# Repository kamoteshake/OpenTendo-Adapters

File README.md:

# OpenTendo-Adapters
Some components of OpenTendo are already obsolete or NRND (Not Recommended for New Design). OpenTendo-Adapters is trying to solve this issue by using a modern equivalent of the OpenTendo components with different footprints and adapting it OpenTendo.

> [!NOTE]
> If for some reason you can't find the components listed in the BOMs and/or decided to find your own, I recommend looking at the `Datasheets` folder. I've included the datasheets of the components used in OEM NES. Look for components that are close to the original component from OEM NES spec wise and that fits on the footprint in the adapters (or you could always fork this and update your own adapter 😉).

## File Structure
```
.
├── <Reference> Adapter  # Contains all files for a specific adapter.
|   |                      "Reference" is based from OpenTendo (i.e. X2 Adapter).
|   ├── BOM              # Contains the bill of materials.
|   ├── Datasheets       # Contains the datasheets of component/s used in the OEM NES
|   |                      on the referenced footprint of OpenTendo.
|   ├── Gerber Files     # Contains The gerber files needed for fabrication.
|   └── KiCad            # Contains all files necessary to open the project in KiCad. 
```

## License
Licensed under the TAPR Open Hardware License ([www.tapr.org/OHL](www.tapr.org/OHL))

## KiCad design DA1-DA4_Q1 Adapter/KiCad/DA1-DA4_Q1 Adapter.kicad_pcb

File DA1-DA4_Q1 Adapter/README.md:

# DA1-DA4 Q1 Adapter
DAN601 and uPA64H have been obsolete for a while. It's been difficult to find diode arrays that are close to DAN601 and uPA64H specs wise. It is easier to build an array from multiple single diodes. Since 2SA937 (Q1 in OpenTendo) is close by the diode arrays and is also obsolete, I decided to just include it in this adapter with a newer component that is somewhat close to 2SA937 spec wise.

## Gerber Files
There are two files in [Gerber Files](./Gerber%20Files/):
1. Single Board - Only consist of just one board.
2. Panelized - Consist of multiple board to fit in a 100mm x 100mm board. The panel have 9 (3x3) adapters. It is panelized using mouse bites.

## Assembly Tips
When soldering the pins, to make sure everything is lined up, put the pin through OpenTendo then put the adapter on the pins and tack some of the header pins before pulling it off from the OpenTendo. You can then finish soldering the pins on the adapter then you can solder the adapter to the OpenTendo.

## Images

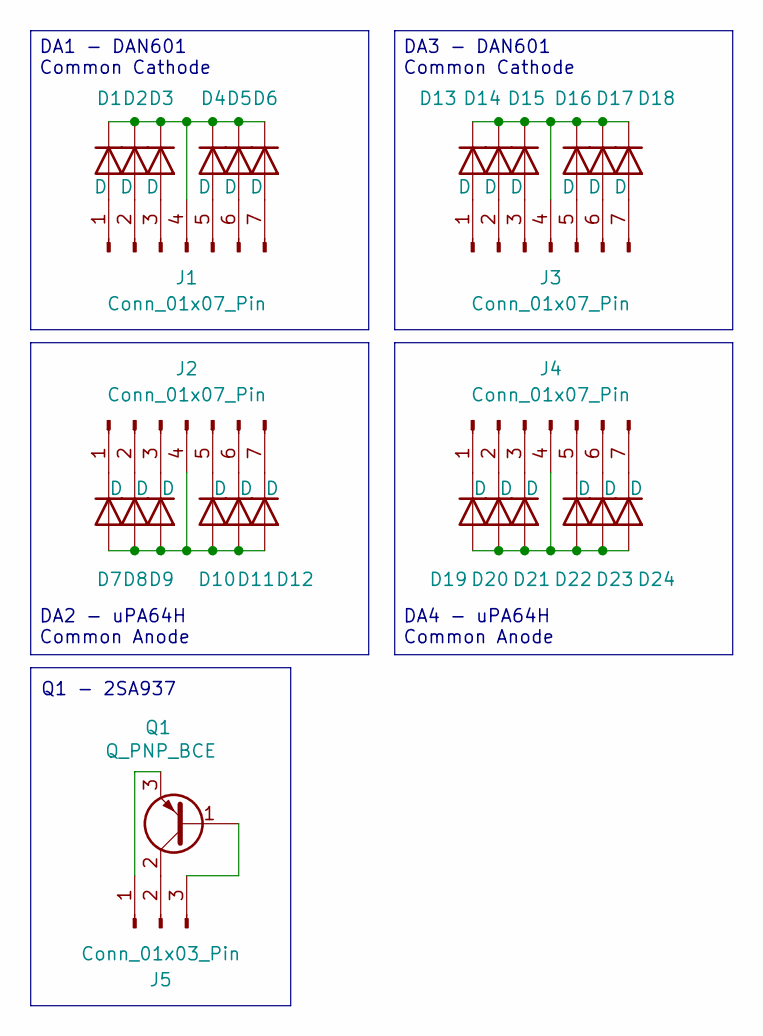
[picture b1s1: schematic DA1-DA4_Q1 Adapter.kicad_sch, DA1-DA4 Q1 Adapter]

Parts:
D1, D2, D3, D4, D5, D6, D7, D8, D9, D10, D11, D12, D13, D14, D15, D16, D17, D18, D19, D20, D21, D22, D23, D24: D; D_SOD-123
J1, J2, J3, J4: Conn_01x07_Pin; R_Array_SIP7
J5: Conn_01x03_Pin; PinHeader_1x03_P2.54mm_Vertical
Q1: Q_PNP_BCE; SOT-89-3

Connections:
unnamed: D1.2 (A), J1.1
unnamed: D1.1 (K), D2.1 (K), D3.1 (K), D4.1 (K), D5.1 (K), D6.1 (K), J1.4
unnamed: D2.2 (A), J1.2
unnamed: D3.2 (A), J1.3
unnamed: D4.2 (A), J1.5
unnamed: D5.2 (A), J1.6
unnamed: D6.2 (A), J1.7
unnamed: D7.1 (K), J2.1
unnamed: D8.1 (K), J2.2
unnamed: D9.1 (K), J2.3
unnamed: D7.2 (A), D8.2 (A), D9.2 (A), D10.2 (A), D11.2 (A), D12.2 (A), J2.4
unnamed: D10.1 (K), J2.5
unnamed: D11.1 (K), J2.6
unnamed: D12.1 (K), J2.7
unnamed: D13.2 (A), J3.1
unnamed: D13.1 (K), D14.1 (K), D15.1 (K), D16.1 (K), D17.1 (K), D18.1 (K), J3.4
unnamed: D14.2 (A), J3.2
unnamed: D15.2 (A), J3.3
unnamed: D16.2 (A), J3.5
unnamed: D17.2 (A), J3.6
unnamed: D18.2 (A), J3.7
unnamed: D19.2 (A), D20.2 (A), D21.2 (A), D22.2 (A), D23.2 (A), D24.2 (A), J4.4
unnamed: D19.1 (K), J4.1
unnamed: D20.1 (K), J4.2
unnamed: D21.1 (K), J4.3
unnamed: D22.1 (K), J4.5
unnamed: D23.1 (K), J4.6
unnamed: D24.1 (K), J4.7
unnamed: J5.1, Q1.3 (E)
unnamed: J5.2, Q1.2 (C)
unnamed: J5.3, Q1.1 (B)

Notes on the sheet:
DA1 - DAN601 Common Cathode
DA4 - uPA64H Common Anode
DA2 - uPA64H Common Anode
Q1 - 2SA937
DA3 - DAN601 Common Cathode

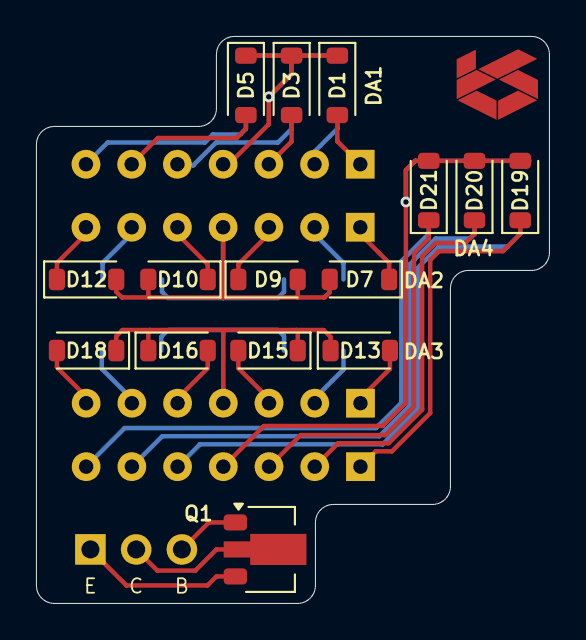
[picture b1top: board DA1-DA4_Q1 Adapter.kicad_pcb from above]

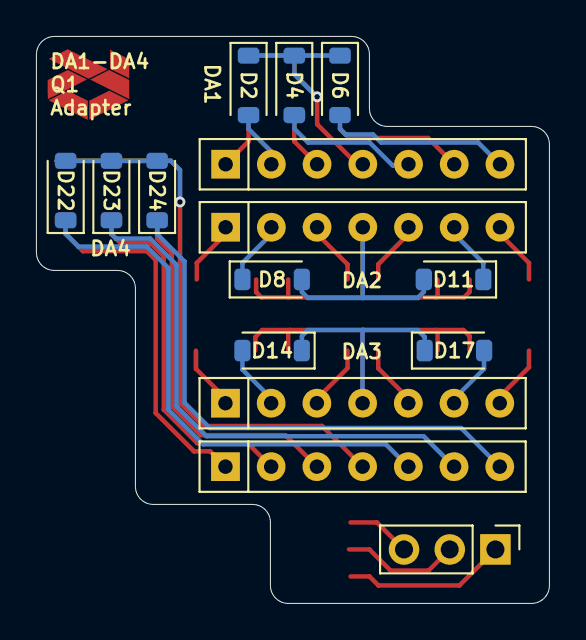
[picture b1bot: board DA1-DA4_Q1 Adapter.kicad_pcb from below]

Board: 2 copper layers, 28.5 x 31.5 mm, 30 parts (15 on the bottom side), 31 nets.

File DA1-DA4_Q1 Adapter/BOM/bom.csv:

Query,Qty,Manufacturer,MPN,Octopart URL,Part Description,Description,Schematic Reference,Internal Part Number,Lifecycle,Lead Time,RoHS,Total Qty (@ Batch Size: 1),SKU,SKU,SKU,SKU,SKU,Packaging,Packaging,Packaging,Packaging,Packaging,Unit Price (@ Batch Size: 1),Unit Price (@ Batch Size: 1),Unit Price (@ Batch Size: 1),Unit Price (@ Batch Size: 1),Unit Price (@ Batch Size: 1),In Stock,In Stock,In Stock,In Stock,In Stock,MOQ,MOQ,MOQ,MOQ,MOQ,URL,URL,URL,URL,URL,Distributor [Lowest Price (Preferred Distributors)],SKU [Lowest Price (Preferred Distributors)],Packaging [Lowest Price (Preferred Distributors)],Unit Price (@ Batch Size: 1) [Lowest Price (Preferred Distributors)],Line Total [Lowest Price (Preferred Distributors)],Batch Total [Lowest Price (Preferred Distributors)],In Stock [Lowest Price (Preferred Distributors)],MOQ [Lowest Price (Preferred Distributors)],URL [Lowest Price (Preferred Distributors)],Notes
,,,,,,,,,,,,,Digi-Key,Mouser,Newark,Onlinecomponents.com,RS Components,Digi-Key,Mouser,Newark,Onlinecomponents.com,RS Components,Digi-Key,Mouser,Newark,Onlinecomponents.com,RS Components,Digi-Key,Mouser,Newark,Onlinecomponents.com,RS Components,Digi-Key,Mouser,Newark,Onlinecomponents.com,RS Components,Digi-Key,Mouser,Newark,Onlinecomponents.com,RS Components,,,,,,,,,,
MBR0580S1-7,12,Diodes Inc.,MBR0580S1-7,https://octopart.com/mbr0580s1-7-diodes+inc.-53081572,"Rectifier Diode, Schottky, 1 Phase, 1 Element, 0.5A, 80V V(RRM), Silicon",,"D1, D2, D3, D4, D5, D6. D13, D14, D15, D16, D17, D18",,,8w,Compliant,12,MBR0580S1-7DICT-ND,621-MBR0580S1-7,07AH4105,,,Cut Tape,Tape & Reel,Cut Tape,,,0.11,0.11,0.037,,,72952,30320,8872,,,1,1,1,,,https://octopart.com/opatz8j6/a1?t=w8CAPHVaSLng70fpFyW7RJQYA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,https://octopart.com/opatz8j6/a1?t=shzPBLAywoVz7eAOx4Vo84RPb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,https://octopart.com/opatz8j6/a1?t=KhZ9j337uodJ78wN1fTlmwmAF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,,,Newark,07AH4105,Cut Tape,0.037,0.44399999999999995,0.44399999999999995,8872,1,https://octopart.com/opatz8j6/a1?t=KhZ9j337uodJ78wN1fTlmwmAF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,
1N4150W-E3-18,12,Vishay,1N4150W-E3-18,https://octopart.com/1n4150w-e3-18-vishay-46456330,Rectifier Diode Small Signal Switching Si 50V 0.2A 4ns 2-Pin SOD-123 T/R,,"D7, D8, D9, D10, D11, D12, D19, D20, D21, D22, D23, D24",,,13w,Compliant,12,1N4150W-E3-18GICT-ND,78-1N4150W-E3-18,09X6132,,,Cut Tape,Tape & Reel,Tape & Reel,,,0.101,0.101,,,,40651,25705,0,,,1,1,10000,,,https://octopart.com/opatz8j6/a1?t=894OLn9BLBn76Nnc499pvUft4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,https://octopart.com/opatz8j6/a1?t=oKEObBrpHRPUW1KcU8mVumPlG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,https://octopart.com/opatz8j6/a1?t=GAg30-IZYFOMRIeTjMKjD1x2p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,,,DigiKey,1N4150W-E3-18GICT-ND,Cut Tape,0.101,1.2120000000000002,1.2120000000000002,40651,1,https://octopart.com/opatz8j6/a1?t=894OLn9BLBn76Nnc499pvUft4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,
2SA2071P5T100Q,1,ROHM,2SA2071P5T100Q,https://octopart.com/2sa2071p5t100q-rohm-75515614,Bipolar Transistors - BJT PNP -3A Ic -60V Vceo MPT3,,Q1,,,13w,Compliant,1,2SA2071P5T100QCT-ND,755-2SA2071P5T100Q,,,,Cut Tape,Tape & Reel,,,,0.91,0.73,,,,2036,3898,,,,1,1,,,,https://octopart.com/opatz8j6/a1?t=SLmwRZgOlMdQ7rE39KG_ThsKs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,https://octopart.com/opatz8j6/a1?t=-ETjDVhYBVl2pT0qtbMhu5Ykh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,,,,Mouser,755-2SA2071P5T100Q,Tape & Reel,0.73,0.73,0.73,3898,1,https://octopart.com/opatz8j6/a1?t=-ETjDVhYBVl2pT0qtbMhu5Ykh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,
10129378-936004BLF,1,Amphenol Communications Solutions,10129378-936004BLF,https://octopart.com/10129378-936004blf-amphenol+communicati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,Header Sr Vt Th 1X36-10129378-936004BLF | Amphenol Fci (amphenol Cs) 10129378936004BLF,Header pins,,,,10w,,1,10129378-936004BLF-ND,649-1012937893604BLF,45AC1146,10129378-936004BLF,,Bulk,Bulk,,Bulk,,0.62,0.65,0.257,,,4802,4678,279,1400,,1,1,1,100,,https://octopart.com/opatz8j6/a1?t=NoxYgr3TMngPRHFvkfCpN2G0_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,https://octopart.com/opatz8j6/a1?t=-7T76Pyw6_Mz5PgNVKfKCDf3b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,https://octopart.com/opatz8j6/a1?t=1TeASPD-WRibQvUAZzXSF_FQq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,https://octopart.com/opatz8j6/a1?t=KH0gDo-eRPVDmRnG-sImXkEJl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,,Newark,45AC1146,,0.257,0.257,0.257,279,1,https://octopart.com/opatz8j6/a1?t=1TeASPD-WRibQvUAZzXSF_FQq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,

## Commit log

2024-11-20 feat: initial commit
2024-11-20 fix: BOM readme
2024-11-20 feat: added kicad version
